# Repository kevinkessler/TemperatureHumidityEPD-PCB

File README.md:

Temperature/Humidity ePaper Display KiCad Files
===============================================
  
In order to investigate the low power modes and techniques for an STM32L0 class microprocessor, I've build a temperature and humidity display using an STM32L031F6 uC, an SI7021 I2C temperature/humidity sensor, and a Waveshare 1.54 inch black, white, and red ePaperDisplay. Starting with a straight-forward, non-optimized version of the software, this project will investigate and document the various power savings techniques that can be applied to the system, in order to get the power usage of the device down to a level that (hopefully) makes it practical to run off of a CR2032 coin cell. 

Track the progress on [Hackaday.io](https://hackaday.io/project/134018-coin-cell-powered-temperaturehumidity-display)

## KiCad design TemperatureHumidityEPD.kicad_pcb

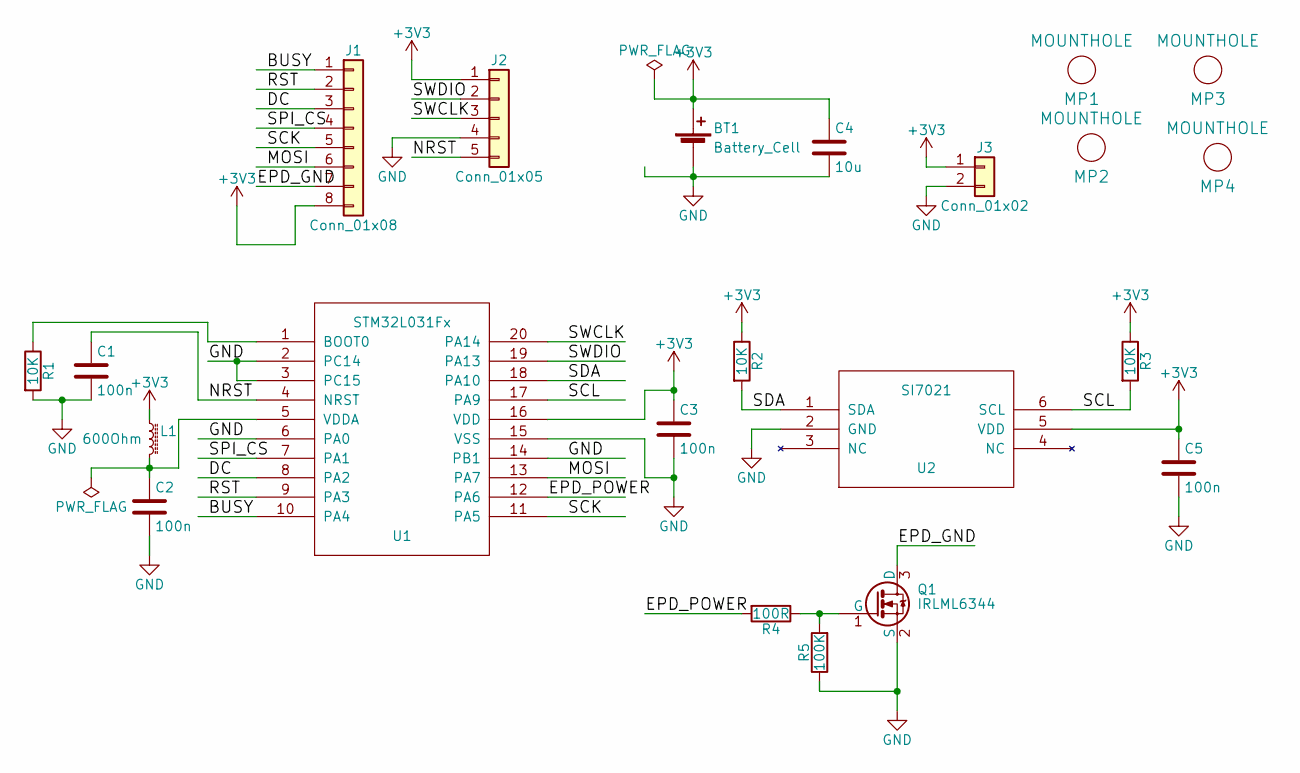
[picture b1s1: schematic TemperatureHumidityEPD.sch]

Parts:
BT1: Battery_Cell; CR2032_BATTERY_HOLDER
C1, C2, C3, C5: 100n; C_0805_HandSoldering
C4: 10u; C_0805_HandSoldering
J1: Conn_01x08; Pin_Header_Straight_1x08_Pitch2.54mm
J2: Conn_01x05; Pin_Header_Straight_1x05_Pitch2.54mm
J3: Conn_01x02; Pin_Header_Straight_1x02_Pitch2.54mm
L1: 600Ohm; R_0805_HandSoldering
MP1, MP2, MP3, MP4: MOUNTHOLE; TH-M3
Q1: IRLML6344; SOT-23
R1, R2, R3: 10K; R_0805_HandSoldering
R4: 100R; R_0805_HandSoldering
R5: 100K; R_0805_HandSoldering
U1: STM32L031Fx; TSSOP-20_4.4x6.5mm_Pitch0.65mm
U2: SI7021

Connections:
+3V3: BT1.1 (+), C3.1, C4.1, C5.1, J1.8, J2.1, J3.1, L1.1, R2.1, R3.1, U1.16 (VDD), U2.5 (VDD)
/BUSY: J1.1, U1.10 (PA4)
/DC: J1.3, U1.8 (PA2)
/EPD_GND: J1.7, Q1.3 (D)
/EPD_POWER: R4.2, U1.12 (PA6)
/MOSI: J1.6, U1.13 (PA7)
/NRST: C1.1, J2.5, U1.4 (NRST)
/RST: J1.2, U1.9 (PA3)
/SCK: J1.5, U1.11 (PA5)
/SCL: R3.2, U1.17 (PA9), U2.6 (SCL)
/SDA: R2.2, U1.18 (PA10), U2.1 (SDA)
/SPI_CS: J1.4, U1.7 (PA1)
/SWCLK: J2.3, U1.20 (PA14)
/SWDIO: J2.2, U1.19 (PA13)
GND: BT1.2 (-), C1.2, C2.2, C3.2, C4.2, C5.2, J2.4, J3.2, Q1.2 (S), R1.2, R5.1, U1.2 (PC14), U1.3 (PC15), U1.6 (PA0), U1.14 (PB1), U1.15 (VSS), U2.2 (GND)
unnamed: C2.1, L1.2, U1.5 (VDDA)
unnamed: Q1.1 (G), R4.1, R5.2
unnamed: R1.1, U1.1 (BOOT0)

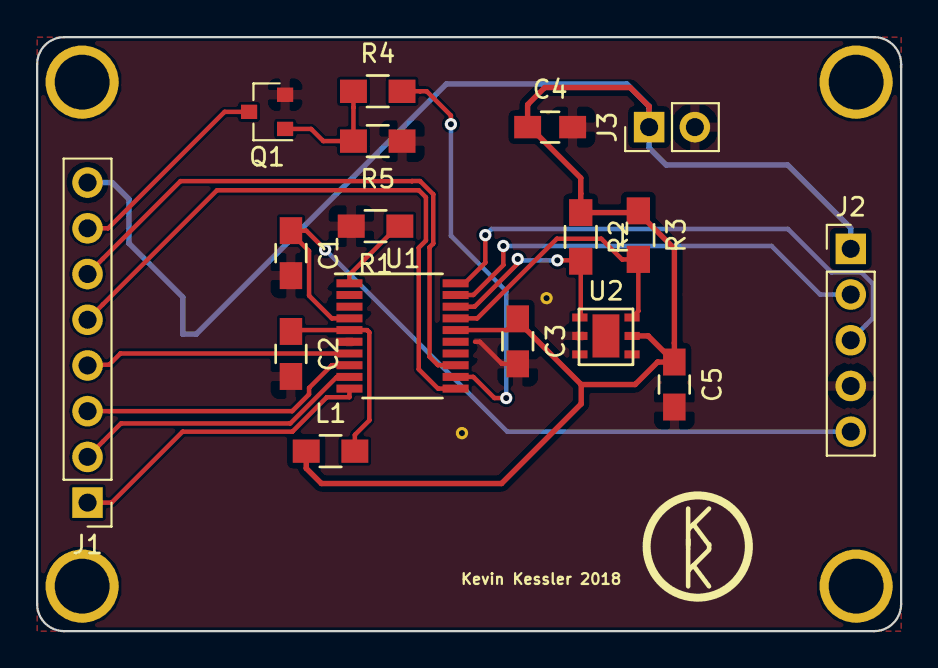
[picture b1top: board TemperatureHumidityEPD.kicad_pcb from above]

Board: 2 copper layers, 48.0 x 33.0 mm, 22 parts (1 on the bottom side), 18 nets.

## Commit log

2018-04-07 Remove BAK File
2018-04-08 Schematic
2018-04-09 PCB Design
2018-07-21 Switching Transistor
2024-01-17 Added License
